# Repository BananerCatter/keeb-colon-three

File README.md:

# keeb-colon-three 
A fully custom 56-key mechanical keyboard, designed from the ground up, including: PCB, case, plate, firmware (No assembly yet). This project was built to learn the entire keyboard design process, as well as to familiarize myself with the necessary tools and software.

## Features:
* 54 key custom ergonomic layout
* MX compatible switches
* Per Key RGB
* Rotary Encoder
* 3D printed tray mount case and plate
* 128x32 OLED display
* RMK firmware

## Why I designed it
Depending on when in the design process I'd ask myself this, I'd get fairly different answers: Because one mechanical keyboard is not enough, because I want to test my patience, because I enjoy suffering. However, beyond all these rather superficial answers, there is one clear truth poking it's head out:

I want to build something meaningful myself. 

This project has given me the opportunity to refine my pcb design, and to learn CAD modelling, manufacturing, firmware configuration, and soon enough, soldering (especially tiny smd components, such as the LEDs and caps) 

## Design Process
The project began quite simple, being a basic 60% keyboard. However, it soon devolved into a split layout (kinda) ergonomic keyboard, featuring rgb, an ec11 and a display module. I designed the PCB in kicad, and routed everything myself, adding a ground copper fill at the end. After that, I designed a relatively simple tray mount case around the PCB, and a plate traced over the F.Courtyard layer of the board.

Firmware was make in rmk, only has layouts and rotary encoder support for now.

## Components
* Custom PCB
* Raspberry Pi Pico (or any footprint compatible rp2040 based board)
* MX-compatible switches
* 3D printed case
* 3D printed or cnc machined plate
* Keycaps
* SK6812 mini-e
* EC11 rotary encoder
* 128x32 OLED display

* All other components mentioned in the bill of materials

## What I learned, what I struggled with.
While I go into way more detail of my struggles in my journal, by far the most difficult parts for me were:

* Designing the case around the board's shape
* Routing while forcing myself to **NOT** use a 4 layer PCB
* Fixing DRC errors that made no sense, such as solder pads existing in their own keepout zones.

What I've learned: 

* PCB design
* Routing
* Basic CAD skills
* How to not lose focus on longer projects
* Miscellaneous KiCAD-related skills.
* Firmware configuration and design.
* A bit of rust :P

What I will learn, once (if) I receive a grant and obtain everything needed for the completed keeb:

* Soldering tiny components
* Even more patience

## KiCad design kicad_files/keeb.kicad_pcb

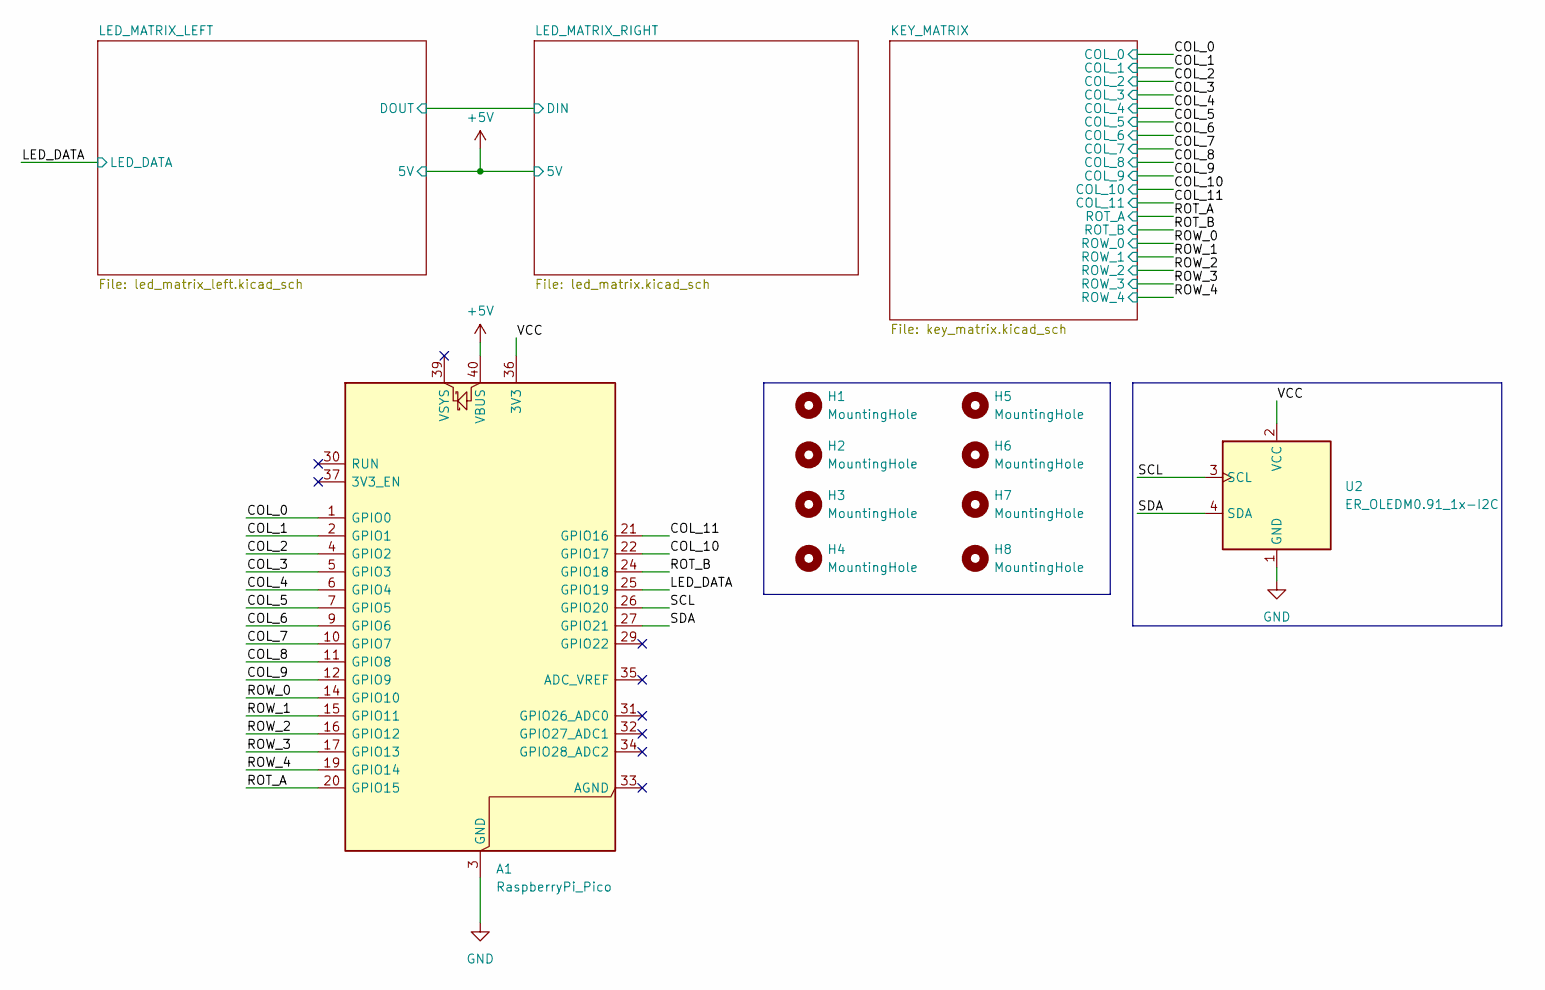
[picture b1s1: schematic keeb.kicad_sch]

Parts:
A1: RaspberryPi_Pico; RaspberryPi_Pico_Common_Unspecified
H1, H2, H3, H4: MountingHole; MountingHole_2.2mm_M2
H5, H6, H7, H8: MountingHole; MountingHole_3.2mm_M3
U2: ER_OLEDM0.91_1x-I2C

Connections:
+5V: A1.40 (VBUS); also elsewhere on the board
/COL_0: A1.1 (GPIO0); also elsewhere on the board
/COL_1: A1.2 (GPIO1); also elsewhere on the board
/COL_2: A1.4 (GPIO2); also elsewhere on the board
/COL_3: A1.5 (GPIO3); also elsewhere on the board
/COL_4: A1.6 (GPIO4); also elsewhere on the board
/COL_5: A1.7 (GPIO5); also elsewhere on the board
/COL_6: A1.9 (GPIO6); also elsewhere on the board
/COL_7: A1.10 (GPIO7); also elsewhere on the board
/COL_8: A1.11 (GPIO8); also elsewhere on the board
/COL_9: A1.12 (GPIO9); also elsewhere on the board
/COL_10: A1.22 (GPIO17); also elsewhere on the board
/COL_11: A1.21 (GPIO16); also elsewhere on the board
/LED_DATA: A1.25 (GPIO19); also elsewhere on the board
/ROT_A: A1.20 (GPIO15); also elsewhere on the board
/ROT_B: A1.24 (GPIO18); also elsewhere on the board
/ROW_0: A1.14 (GPIO10); also elsewhere on the board
/ROW_1: A1.15 (GPIO11); also elsewhere on the board
/ROW_2: A1.16 (GPIO12); also elsewhere on the board
/ROW_3: A1.17 (GPIO13); also elsewhere on the board
/ROW_4: A1.19 (GPIO14); also elsewhere on the board
/SCL: A1.26 (GPIO20), U2.3 (SCL)
/SDA: A1.27 (GPIO21), U2.4 (SDA)
/VCC: A1.36 (3V3), U2.2 (VCC)
GND: A1.3 (GND), A1.8 (GND), A1.13 (GND), A1.18 (GND), A1.23 (GND), A1.28 (GND), A1.38 (GND), U2.1 (GND); also elsewhere on the board

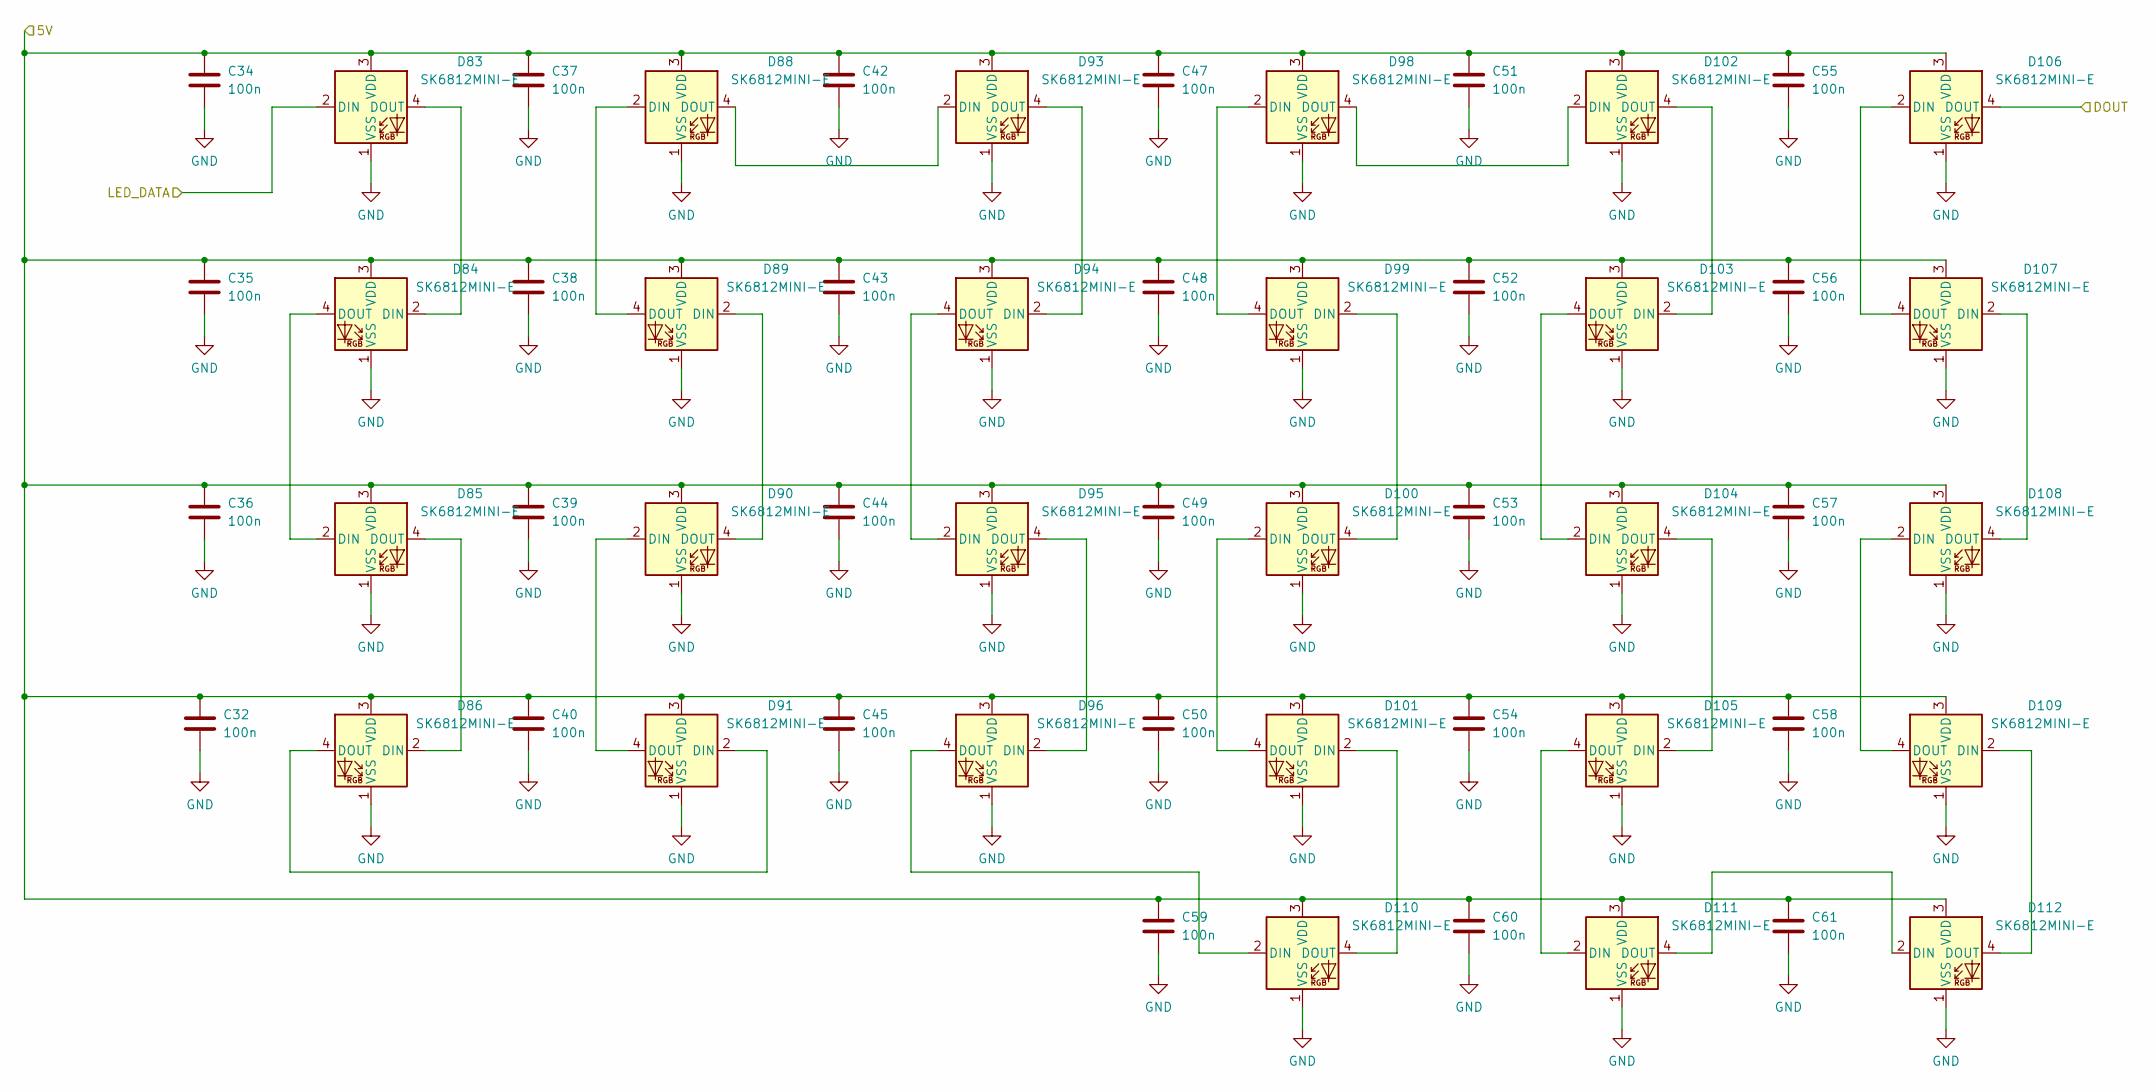
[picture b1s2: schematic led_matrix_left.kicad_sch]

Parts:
C32, C34, C35, C36, C37, C38, C39, C40, C42, C43, C44, C45, C47, C48, C49, C50, C51, C52, C53, C54, C55, C56, C57, C58, C59, C60, C61: 100n; C_0603_1608Metric_Pad1.08x0.95mm_HandSolder
D83, D84, D85, D86, D88, D89, D90, D91, D93, D94, D95, D96, D98, D99, D100, D101, D102, D103, D104, D105, D106, D107, D108, D109, D110, D111, D112: SK6812MINI-E; LED_SK6812MINI-E_3.2x2.8mm_P1.5mm_ReverseMount

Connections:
+5V: C32.1, C34.1, C35.1, C36.1, C37.1, C38.1, C39.1, C40.1, C42.1, C43.1, C44.1, C45.1, C47.1, C48.1, C49.1, C50.1, C51.1, C52.1, C53.1, C54.1, C55.1, C56.1, C57.1, C58.1, C59.1, C60.1, C61.1, D83.3 (VDD), D84.3 (VDD), D85.3 (VDD), D86.3 (VDD), D88.3 (VDD), D89.3 (VDD), D90.3 (VDD), D91.3 (VDD), D93.3 (VDD), D94.3 (VDD), D95.3 (VDD), D96.3 (VDD), D98.3 (VDD), D99.3 (VDD), D100.3 (VDD), D101.3 (VDD), D102.3 (VDD), D103.3 (VDD), D104.3 (VDD), D105.3 (VDD), D106.3 (VDD), D107.3 (VDD), D108.3 (VDD), D109.3 (VDD), D110.3 (VDD), D111.3 (VDD), D112.3 (VDD); also elsewhere on the board
/LED_DATA: D83.2 (DIN); also elsewhere on the board
/LED_MATRIX_LEFT/DOUT: D106.4 (DOUT); also elsewhere on the board
GND: C32.2, C34.2, C35.2, C36.2, C37.2, C38.2, C39.2, C40.2, C42.2, C43.2, C44.2, C45.2, C47.2, C48.2, C49.2, C50.2, C51.2, C52.2, C53.2, C54.2, C55.2, C56.2, C57.2, C58.2, C59.2, C60.2, C61.2, D83.1 (VSS), D84.1 (VSS), D85.1 (VSS), D86.1 (VSS), D88.1 (VSS), D89.1 (VSS), D90.1 (VSS), D91.1 (VSS), D93.1 (VSS), D94.1 (VSS), D95.1 (VSS), D96.1 (VSS), D98.1 (VSS), D99.1 (VSS), D100.1 (VSS), D101.1 (VSS), D102.1 (VSS), D103.1 (VSS), D104.1 (VSS), D105.1 (VSS), D106.1 (VSS), D107.1 (VSS), D108.1 (VSS), D109.1 (VSS), D110.1 (VSS), D111.1 (VSS), D112.1 (VSS); also elsewhere on the board
unnamed: D83.4 (DOUT), D84.2 (DIN)
unnamed: D84.4 (DOUT), D85.2 (DIN)
unnamed: D85.4 (DOUT), D86.2 (DIN)
unnamed: D86.4 (DOUT), D91.2 (DIN)
unnamed: D88.2 (DIN), D89.4 (DOUT)
unnamed: D88.4 (DOUT), D93.2 (DIN)
unnamed: D89.2 (DIN), D90.4 (DOUT)
unnamed: D90.2 (DIN), D91.4 (DOUT)
unnamed: D93.4 (DOUT), D94.2 (DIN)
unnamed: D94.4 (DOUT), D95.2 (DIN)
unnamed: D95.4 (DOUT), D96.2 (DIN)
unnamed: D98.2 (DIN), D99.4 (DOUT)
unnamed: D100.2 (DIN), D101.4 (DOUT)
unnamed: D99.2 (DIN), D100.4 (DOUT)
unnamed: D101.2 (DIN), D110.4 (DOUT)
unnamed: D98.4 (DOUT), D102.2 (DIN)
unnamed: D102.4 (DOUT), D103.2 (DIN)
unnamed: D103.4 (DOUT), D104.2 (DIN)
unnamed: D104.4 (DOUT), D105.2 (DIN)
unnamed: D105.4 (DOUT), D111.2 (DIN)
unnamed: D106.2 (DIN), D107.4 (DOUT)
unnamed: D107.2 (DIN), D108.4 (DOUT)
unnamed: D108.2 (DIN), D109.4 (DOUT)
unnamed: D109.2 (DIN), D112.4 (DOUT)
unnamed: D96.4 (DOUT), D110.2 (DIN)
unnamed: D111.4 (DOUT), D112.2 (DIN)

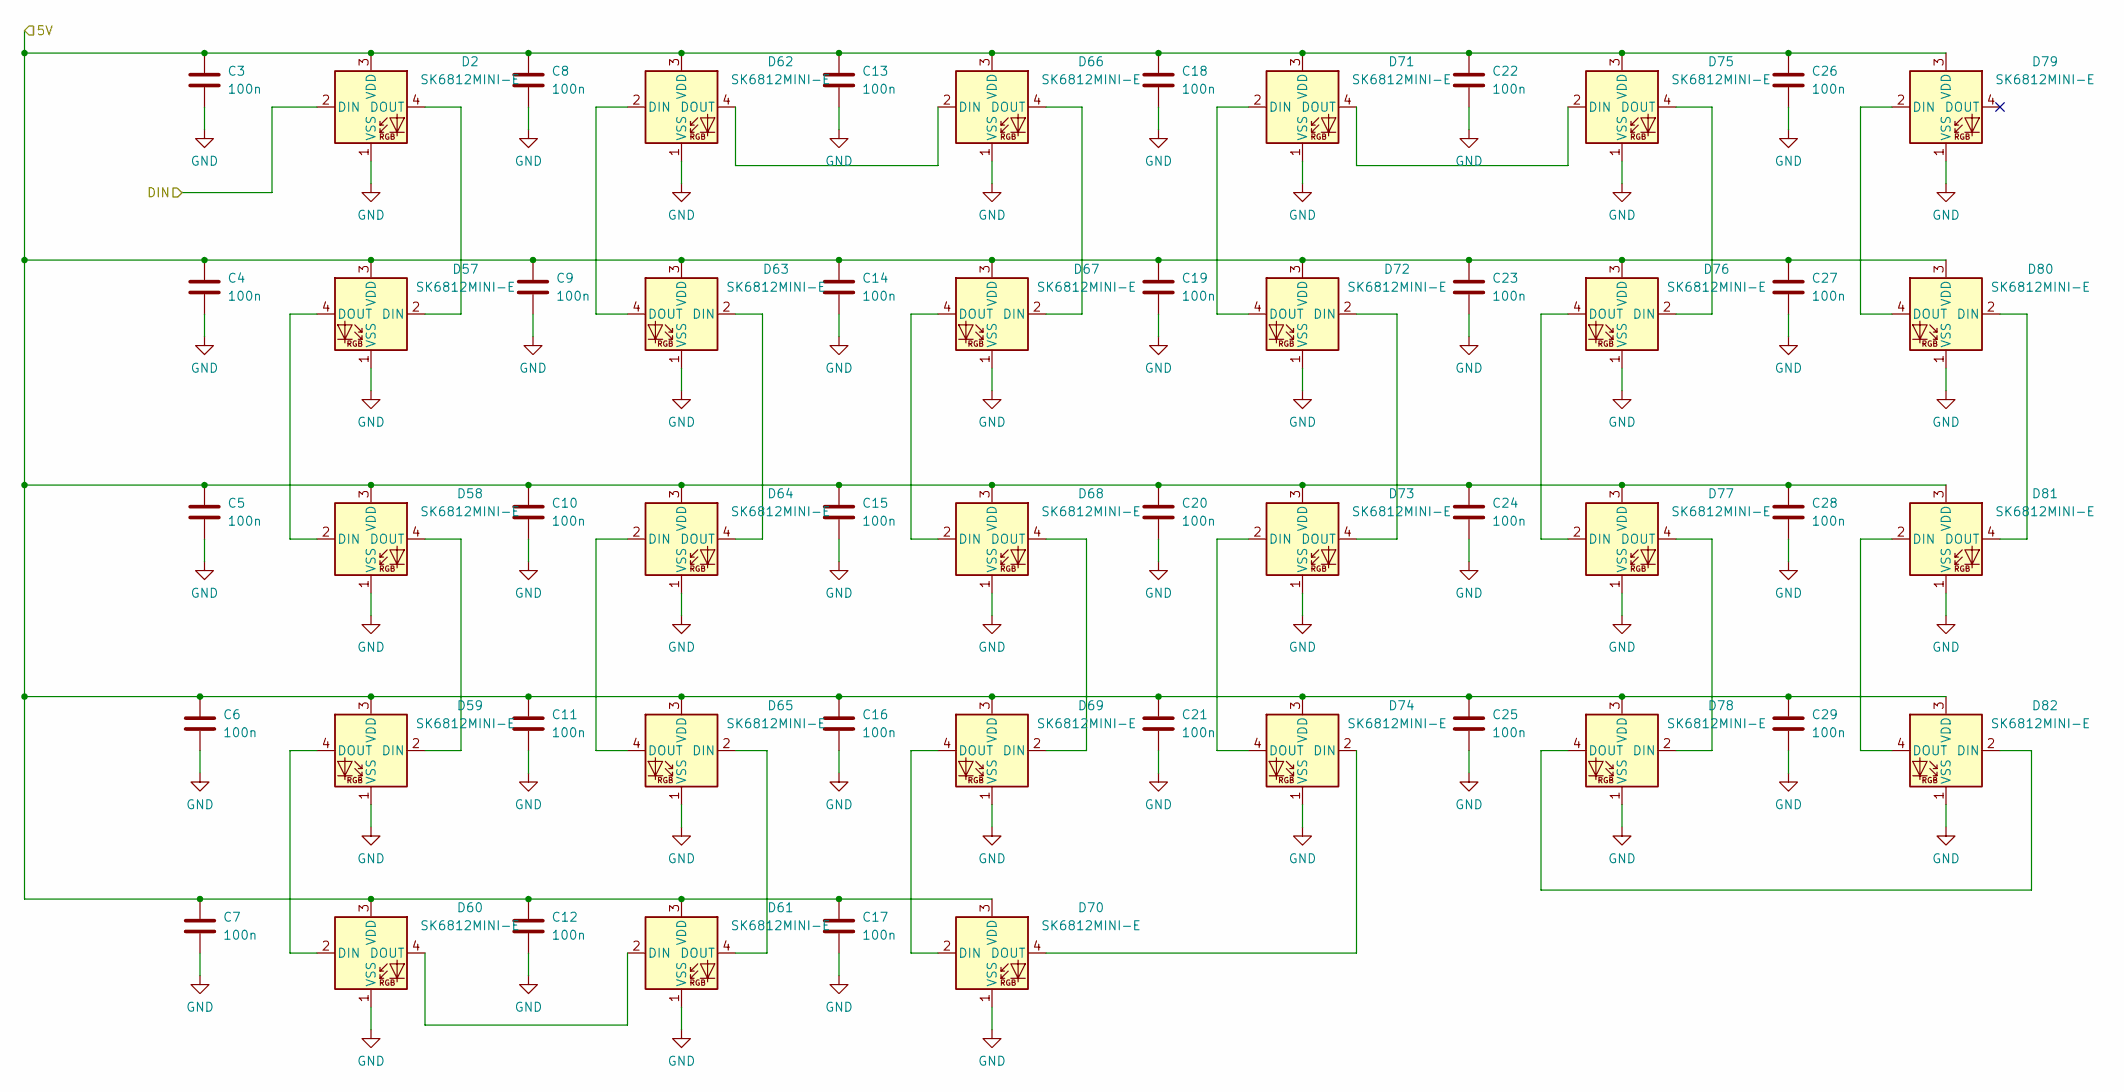
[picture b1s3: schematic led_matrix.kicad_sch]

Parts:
C3, C4, C5, C6, C7, C8, C9, C10, C11, C12, C13, C14, C15, C16, C17, C18, C19, C20, C21, C22, C23, C24, C25, C26, C27, C28, C29: 100n; C_0603_1608Metric_Pad1.08x0.95mm_HandSolder
D2, D57, D58, D59, D60, D61, D62, D63, D64, D65, D66, D67, D68, D69, D70, D71, D72, D73, D74, D75, D76, D77, D78, D79, D80, D81, D82: SK6812MINI-E; LED_SK6812MINI-E_3.2x2.8mm_P1.5mm_ReverseMount

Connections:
+5V: C3.1, C4.1, C5.1, C6.1, C7.1, C8.1, C9.1, C10.1, C11.1, C12.1, C13.1, C14.1, C15.1, C16.1, C17.1, C18.1, C19.1, C20.1, C21.1, C22.1, C23.1, C24.1, C25.1, C26.1, C27.1, C28.1, C29.1, D2.3 (VDD), D57.3 (VDD), D58.3 (VDD), D59.3 (VDD), D60.3 (VDD), D61.3 (VDD), D62.3 (VDD), D63.3 (VDD), D64.3 (VDD), D65.3 (VDD), D66.3 (VDD), D67.3 (VDD), D68.3 (VDD), D69.3 (VDD), D70.3 (VDD), D71.3 (VDD), D72.3 (VDD), D73.3 (VDD), D74.3 (VDD), D75.3 (VDD), D76.3 (VDD), D77.3 (VDD), D78.3 (VDD), D79.3 (VDD), D80.3 (VDD), D81.3 (VDD), D82.3 (VDD); also elsewhere on the board
/LED_MATRIX_LEFT/DOUT: D2.2 (DIN); also elsewhere on the board
GND: C3.2, C4.2, C5.2, C6.2, C7.2, C8.2, C9.2, C10.2, C11.2, C12.2, C13.2, C14.2, C15.2, C16.2, C17.2, C18.2, C19.2, C20.2, C21.2, C22.2, C23.2, C24.2, C25.2, C26.2, C27.2, C28.2, C29.2, D2.1 (VSS), D57.1 (VSS), D58.1 (VSS), D59.1 (VSS), D60.1 (VSS), D61.1 (VSS), D62.1 (VSS), D63.1 (VSS), D64.1 (VSS), D65.1 (VSS), D66.1 (VSS), D67.1 (VSS), D68.1 (VSS), D69.1 (VSS), D70.1 (VSS), D71.1 (VSS), D72.1 (VSS), D73.1 (VSS), D74.1 (VSS), D75.1 (VSS), D76.1 (VSS), D77.1 (VSS), D78.1 (VSS), D79.1 (VSS), D80.1 (VSS), D81.1 (VSS), D82.1 (VSS); also elsewhere on the board
unnamed: D2.4 (DOUT), D57.2 (DIN)
unnamed: D57.4 (DOUT), D58.2 (DIN)
unnamed: D58.4 (DOUT), D59.2 (DIN)
unnamed: D59.4 (DOUT), D60.2 (DIN)
unnamed: D60.4 (DOUT), D61.2 (DIN)
unnamed: D61.4 (DOUT), D65.2 (DIN)
unnamed: D62.2 (DIN), D63.4 (DOUT)
unnamed: D62.4 (DOUT), D66.2 (DIN)
unnamed: D63.2 (DIN), D64.4 (DOUT)
unnamed: D64.2 (DIN), D65.4 (DOUT)
unnamed: D66.4 (DOUT), D67.2 (DIN)
unnamed: D67.4 (DOUT), D68.2 (DIN)
unnamed: D68.4 (DOUT), D69.2 (DIN)
unnamed: D69.4 (DOUT), D70.2 (DIN)
unnamed: D70.4 (DOUT), D74.2 (DIN)
unnamed: D71.2 (DIN), D72.4 (DOUT)
unnamed: D71.4 (DOUT), D75.2 (DIN)
unnamed: D72.2 (DIN), D73.4 (DOUT)
unnamed: D73.2 (DIN), D74.4 (DOUT)
unnamed: D75.4 (DOUT), D76.2 (DIN)
unnamed: D76.4 (DOUT), D77.2 (DIN)
unnamed: D77.4 (DOUT), D78.2 (DIN)
unnamed: D78.4 (DOUT), D82.2 (DIN)
unnamed: D79.2 (DIN), D80.4 (DOUT)
unnamed: D80.2 (DIN), D81.4 (DOUT)
unnamed: D81.2 (DIN), D82.4 (DOUT)

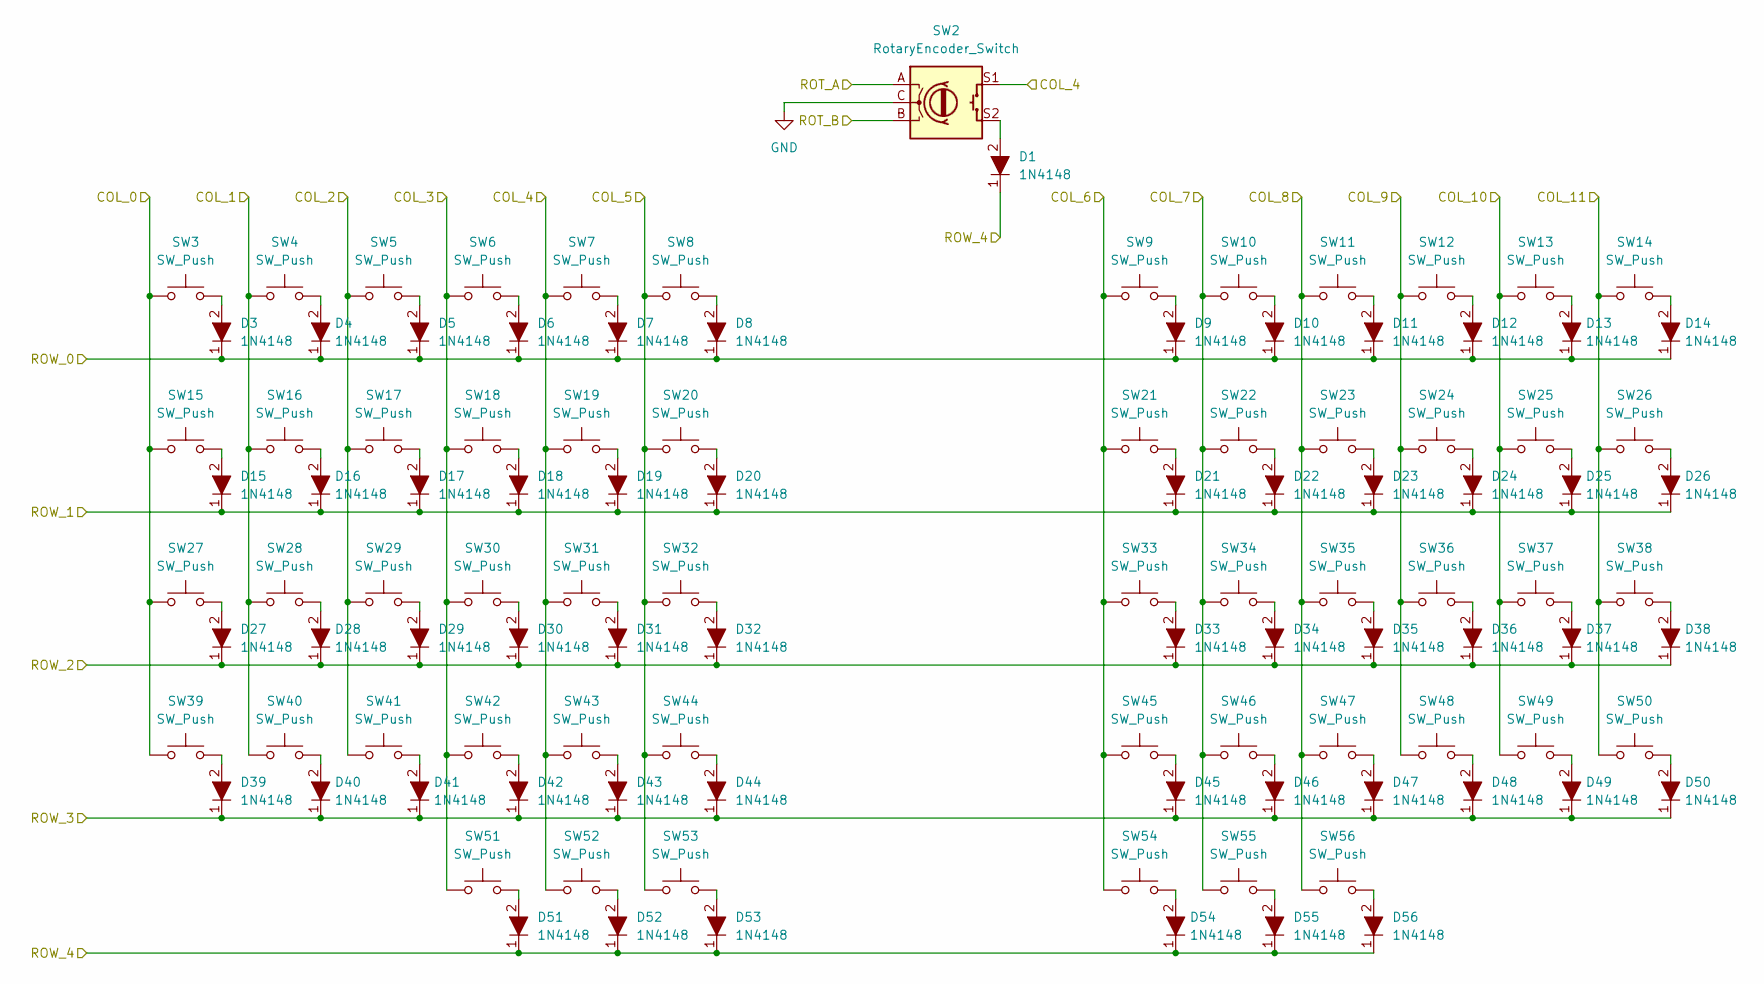
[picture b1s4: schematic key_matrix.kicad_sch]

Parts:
D1, D3, D4, D5, D6, D7, D8, D9, D10, D11, D12, D13, D14, D15, D16, D17, D18, D19, D20, D21, D22, D23, D24, D25, D26, D27, D28, D29, D30, D31, D32, D33, D34, D35, D36, D37, D38, D39, D40, D41, D42, D43, D44, D45, D46, D47, D48, D49, D50, D51, D52, D53, D54, D55, D56: 1N4148; D_DO-35_SOD27_P7.62mm_Horizontal; MPN 1N4148; Digi-Key_PN 1N4148FS-ND
SW2: RotaryEncoder_Switch; RotaryEncoder_Alps_EC11E-Switch_Vertical_H20mm
SW3, SW4, SW5, SW6, SW7, SW8, SW9, SW10, SW11, SW12, SW13, SW14, SW15, SW16, SW17, SW18, SW19, SW20, SW21, SW22, SW23, SW24, SW25, SW26, SW27, SW28, SW29, SW30, SW31, SW32, SW33, SW34, SW35, SW36, SW37, SW38, SW39, SW40, SW41, SW42, SW43, SW44, SW45, SW46, SW47, SW48, SW49, SW50, SW51, SW52, SW53, SW54, SW55, SW56: SW_Push; SW_MX_1u

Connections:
/COL_0: SW3.1, SW15.1, SW27.1, SW39.1; also elsewhere on the board
/COL_1: SW4.1, SW16.1, SW28.1, SW40.1; also elsewhere on the board
/COL_2: SW5.1, SW17.1, SW29.1, SW41.1; also elsewhere on the board
/COL_3: SW6.1, SW18.1, SW30.1, SW42.1, SW51.1; also elsewhere on the board
/COL_4: SW2.S1, SW7.1, SW19.1, SW31.1, SW43.1, SW52.1; also elsewhere on the board
/COL_5: SW8.1, SW20.1, SW32.1, SW44.1, SW53.1; also elsewhere on the board
/COL_6: SW9.1, SW21.1, SW33.1, SW45.1, SW54.1; also elsewhere on the board
/COL_7: SW10.1, SW22.1, SW34.1, SW46.1, SW55.1; also elsewhere on the board
/COL_8: SW11.1, SW23.1, SW35.1, SW47.1, SW56.1; also elsewhere on the board
/COL_9: SW12.1, SW24.1, SW36.1, SW48.1; also elsewhere on the board
/COL_10: SW13.1, SW25.1, SW37.1, SW49.1; also elsewhere on the board
/COL_11: SW14.1, SW26.1, SW38.1, SW50.1; also elsewhere on the board
/ROT_A: SW2.A; also elsewhere on the board
/ROT_B: SW2.B; also elsewhere on the board
/ROW_0: D3.1, D4.1, D5.1, D6.1, D7.1, D8.1, D9.1, D10.1, D11.1, D12.1, D13.1, D14.1; also elsewhere on the board
/ROW_1: D15.1, D16.1, D17.1, D18.1, D19.1, D20.1, D21.1, D22.1, D23.1, D24.1, D25.1, D26.1; also elsewhere on the board
/ROW_2: D27.1, D28.1, D29.1, D30.1, D31.1, D32.1, D33.1, D34.1, D35.1, D36.1, D37.1, D38.1; also elsewhere on the board
/ROW_3: D39.1, D40.1, D41.1, D42.1, D43.1, D44.1, D45.1, D46.1, D47.1, D48.1, D49.1, D50.1; also elsewhere on the board
/ROW_4: D1.1, D51.1, D52.1, D53.1, D54.1, D55.1, D56.1; also elsewhere on the board
GND: SW2.C; also elsewhere on the board
unnamed: D1.2, SW2.S2
unnamed: D3.2, SW3.2
unnamed: D4.2, SW4.2
unnamed: D5.2, SW5.2
unnamed: D6.2, SW6.2
unnamed: D7.2, SW7.2
unnamed: D8.2, SW8.2
unnamed: D9.2, SW9.2
unnamed: D10.2, SW10.2
unnamed: D11.2, SW11.2
unnamed: D12.2, SW12.2
unnamed: D13.2, SW13.2
unnamed: D14.2, SW14.2
unnamed: D15.2, SW15.2
unnamed: D16.2, SW16.2
unnamed: D17.2, SW17.2
unnamed: D18.2, SW18.2
unnamed: D19.2, SW19.2
unnamed: D20.2, SW20.2
unnamed: D21.2, SW21.2
unnamed: D22.2, SW22.2
unnamed: D23.2, SW23.2
unnamed: D24.2, SW24.2
unnamed: D25.2, SW25.2
unnamed: D26.2, SW26.2
unnamed: D27.2, SW27.2
unnamed: D28.2, SW28.2
unnamed: D29.2, SW29.2
unnamed: D30.2, SW30.2
unnamed: D31.2, SW31.2
unnamed: D32.2, SW32.2
unnamed: D33.2, SW33.2
unnamed: D34.2, SW34.2
unnamed: D35.2, SW35.2
unnamed: D36.2, SW36.2
unnamed: D37.2, SW37.2
unnamed: D38.2, SW38.2
unnamed: D39.2, SW39.2
unnamed: D40.2, SW40.2
unnamed: D41.2, SW41.2
unnamed: D42.2, SW42.2
unnamed: D43.2, SW43.2
unnamed: D44.2, SW44.2
unnamed: D45.2, SW45.2
unnamed: D46.2, SW46.2
unnamed: D47.2, SW47.2
unnamed: D48.2, SW48.2
unnamed: D49.2, SW49.2
unnamed: D50.2, SW50.2
unnamed: D51.2, SW51.2
unnamed: D52.2, SW52.2
unnamed: D53.2, SW53.2
unnamed: D54.2, SW54.2
unnamed: D55.2, SW55.2
unnamed: D56.2, SW56.2

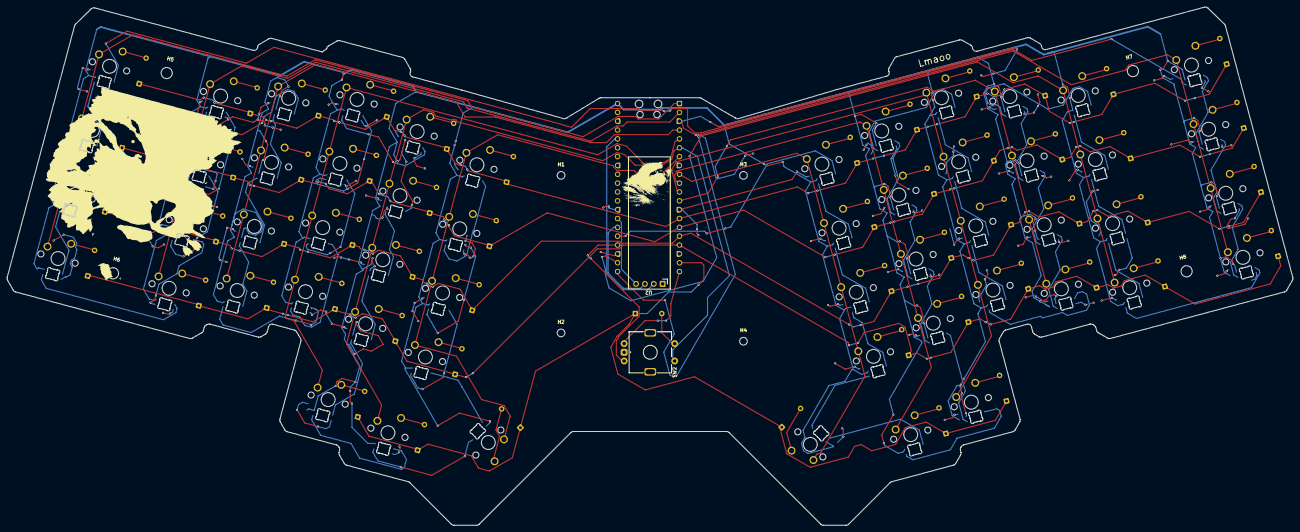
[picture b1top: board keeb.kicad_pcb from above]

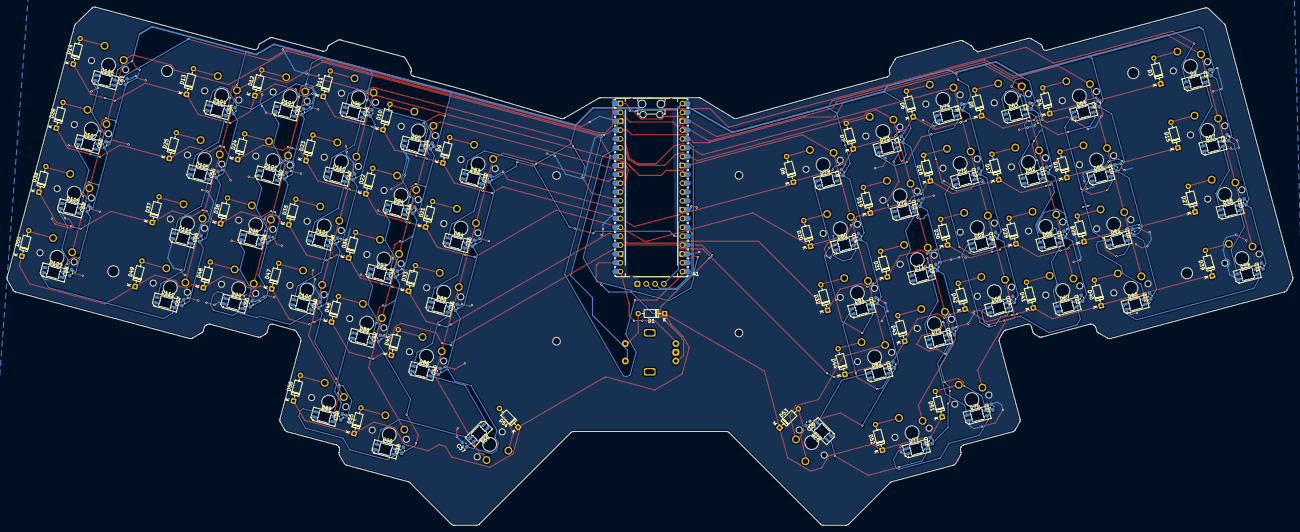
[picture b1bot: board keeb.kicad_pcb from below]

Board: 2 copper layers, 369.3 x 148.8 mm, 228 parts (164 on the bottom side), 133 nets.

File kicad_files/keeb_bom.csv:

"Id";"Designator";"Footprint";"Quantity";"Designation";"Supplier and ref";
1;"A1";"RaspberryPi_Pico_Common_Unspecified";1;"RaspberryPi_Pico";;;
2;"C3, C4, C5, C6, C7, C8, C9, C10, C11, C12, C13, C14, C15, C16, C17, C18, C19, C20, C21, C22, C23, C24, C25, C26, C27, C28, C29, C32, C34, C35, C36, C37, C38, C39, C40, C42, C43, C44, C45, C47, C48, C49, C50, C51, C52, C53, C54, C55, C56, C57, C58, C59, C60, C61";"C_0603_1608Metric_Pad1.08x0.95mm_HandSolder";54;"100n";;;
3;"D1, D3, D4, D5, D6, D7, D8, D9, D10, D11, D12, D13, D14, D15, D16, D17, D18, D19, D20, D21, D22, D23, D24, D25, D26, D27, D28, D29, D30, D31, D32, D33, D34, D35, D36, D37, D38, D39, D40, D41, D42, D43, D44, D45, D46, D47, D48, D49, D50, D51, D52, D53, D54, D55, D56";"D_DO-35_SOD27_P7.62mm_Horizontal";55;"1N4148";;;
4;"D2, D57, D58, D59, D60, D61, D62, D63, D64, D65, D66, D67, D68, D69, D70, D71, D72, D73, D74, D75, D76, D77, D78, D79, D80, D81, D82, D83, D84, D85, D86, D88, D89, D90, D91, D93, D94, D95, D96, D98, D99, D100, D101, D102, D103, D104, D105, D106, D107, D108, D109, D110, D111, D112";"LED_SK6812MINI-E_3.2x2.8mm_P1.5mm_ReverseMount";54;"SK6812MINI-E";;;
5;"S1, S2";"STAB_MX_2u";2;"MX_stab";;;
6;"SW2";"RotaryEncoder_Alps_EC11E-Switch_Vertical_H20mm";1;"RotaryEncoder_Switch";;;
7;"SW3, SW4, SW5, SW6, SW7, SW8, SW9, SW10, SW11, SW12, SW13, SW14, SW15, SW16, SW17, SW18, SW19, SW20, SW21, SW22, SW23, SW24, SW25, SW26, SW27, SW28, SW29, SW30, SW31, SW32, SW33, SW34, SW35, SW36, SW37, SW38, SW39, SW40, SW41, SW42, SW43, SW44, SW45, SW46, SW47, SW48, SW49, SW50, SW51, SW52, SW53, SW54, SW55, SW56";"SW_MX_1u";54;"SW_Push";;;
8;"U2";"ER_OLEDM0.91_1x-I2C";1;"ER_OLEDM0.91_1x-I2C";;;
